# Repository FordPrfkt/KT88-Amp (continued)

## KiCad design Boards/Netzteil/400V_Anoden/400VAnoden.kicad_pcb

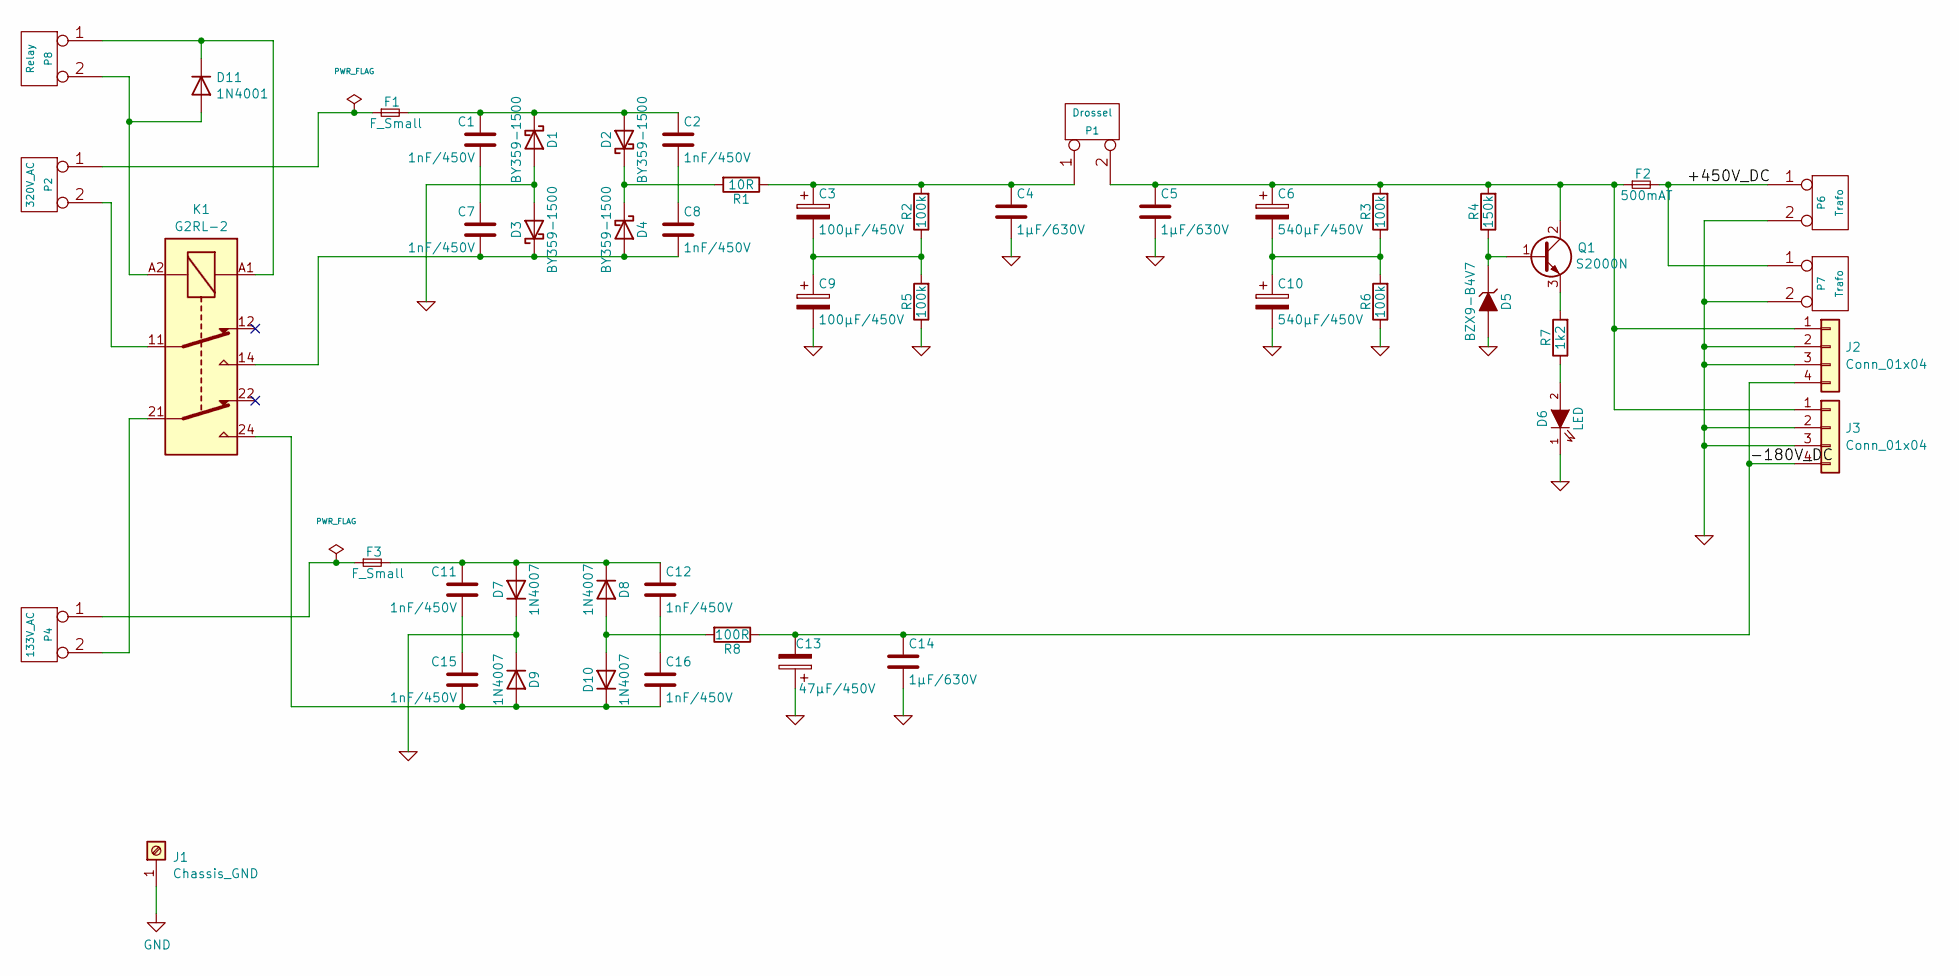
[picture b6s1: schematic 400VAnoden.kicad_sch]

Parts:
C1, C2, C7, C8, C11, C12, C15, C16: 1nF/450V; C_Rect_L10.0mm_W4.0mm_P7.50mm_FKS3_FKP3
C3, C9: 100µF/450V; CP_Radial_D22.0mm_P10.00mm_SnapIn
C4, C5, C14: 1µF/630V; C_Rect_L31.5mm_W11.0mm_P27.50mm_MKS4
C6, C10: 540µF/450V; CP_Radial_D35.0mm_P10.00mm_SnapIn
C13: 47µF/450V; CP_Radial_D16.0mm_P7.50mm
D1, D2, D3, D4: BY359-1500; TO-220-2_Vertical
D5: BZX9-B4V7; D_DO-35_SOD27_P10.16mm_Horizontal
D6: LED; LED_D5.0mm
D7, D8, D9, D10: 1N4007; D_DO-41_SOD81_P10.16mm_Horizontal
D11: 1N4001; D_DO-41_SOD81_P10.16mm_Horizontal
F1, F3: F_Small; Fuse__Holder_Eska_509100
F2: 500mAT; Fuse__Holder_Eska_509100
J1: Chassis_GND; MountingHole_3.2mm_M3_Pad_Via
J2, J3: Conn_01x04; Molex_Mini-Fit_Jr_5566-04A_2x02_P4.20mm_Vertical
K1: G2RL-2; Relay_DPDT_Omron_G2RL-2
P1: Drossel; Molex_Mini-Fit_Jr_5566-02A_2x01_P4.20mm_Vertical
P2: 320V_AC; Molex_Mini-Fit_Jr_5566-02A_2x01_P4.20mm_Vertical
P4: 133V_AC; Molex_Mini-Fit_Jr_5566-02A_2x01_P4.20mm_Vertical
P6, P7: Trafo; Molex_Mini-Fit_Jr_5566-02A_2x01_P4.20mm_Vertical
P8: Relay; Molex_KK-254_AE-6410-02A_1x02_P2.54mm_Vertical
Q1: S2000N; TO-3P-3_Horizontal_TabDown
R1: 10R; R_Axial_DIN0207_L6.3mm_D2.5mm_P10.16mm_Horizontal
R2, R3, R5, R6: 100k; R_Axial_DIN0207_L6.3mm_D2.5mm_P10.16mm_Horizontal
R4: 150k; R_Axial_DIN0207_L6.3mm_D2.5mm_P10.16mm_Horizontal
R7: 1k2; R_Axial_DIN0414_L11.9mm_D4.5mm_P15.24mm_Horizontal
R8: 100R; R_Axial_DIN0207_L6.3mm_D2.5mm_P10.16mm_Horizontal

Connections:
/+450V_DC: F2.2, P6.1, P7.1
/-180V_DC: C13.2, C14.1, J2.4, J3.4, R8.1
GND: C4.2, C5.2, C9.2, C10.2, C13.1, C14.2, D1.2 (A), D3.2 (A), D5.2 (A), D6.1 (K), D7.1 (K), D9.1 (K), J1.1, J2.2, J2.3, J3.2, J3.3, P6.2, P7.2, R5.1, R6.1
unnamed: C1.2, C7.1
unnamed: C2.2, C8.1
unnamed: C3.2, C9.1, R2.1, R5.2
unnamed: C6.2, C10.1, R3.1, R6.2
unnamed: C11.2, C15.1
unnamed: C12.2, C16.1
unnamed: C1.1, C2.1, D1.1 (K), D2.2 (A), F1.2
unnamed: D2.1 (K), D4.1 (K), R1.2
unnamed: C7.2, C8.2, D3.1 (K), D4.2 (A), K1.14
unnamed: D5.1 (K), Q1.1 (B), R4.1
unnamed: D6.2 (A), R7.1
unnamed: C11.1, C12.1, D7.2 (A), D8.1 (K), F3.2
unnamed: D8.2 (A), D10.2 (A), R8.2
unnamed: C15.2, C16.2, D9.2 (A), D10.1 (K), K1.24
unnamed: D11.2 (A), K1.A2, P8.2
unnamed: D11.1 (K), K1.A1, P8.1
unnamed: C5.1, C6.1, F2.1, J2.1, J3.1, P1.2, Q1.2 (C), R3.2, R4.2
unnamed: C3.1, C4.1, P1.1, R1.1, R2.2
unnamed: F1.1, P2.1
unnamed: K1.11, P2.2
unnamed: F3.1, P4.1
unnamed: K1.21, P4.2
unnamed: Q1.3 (E), R7.2

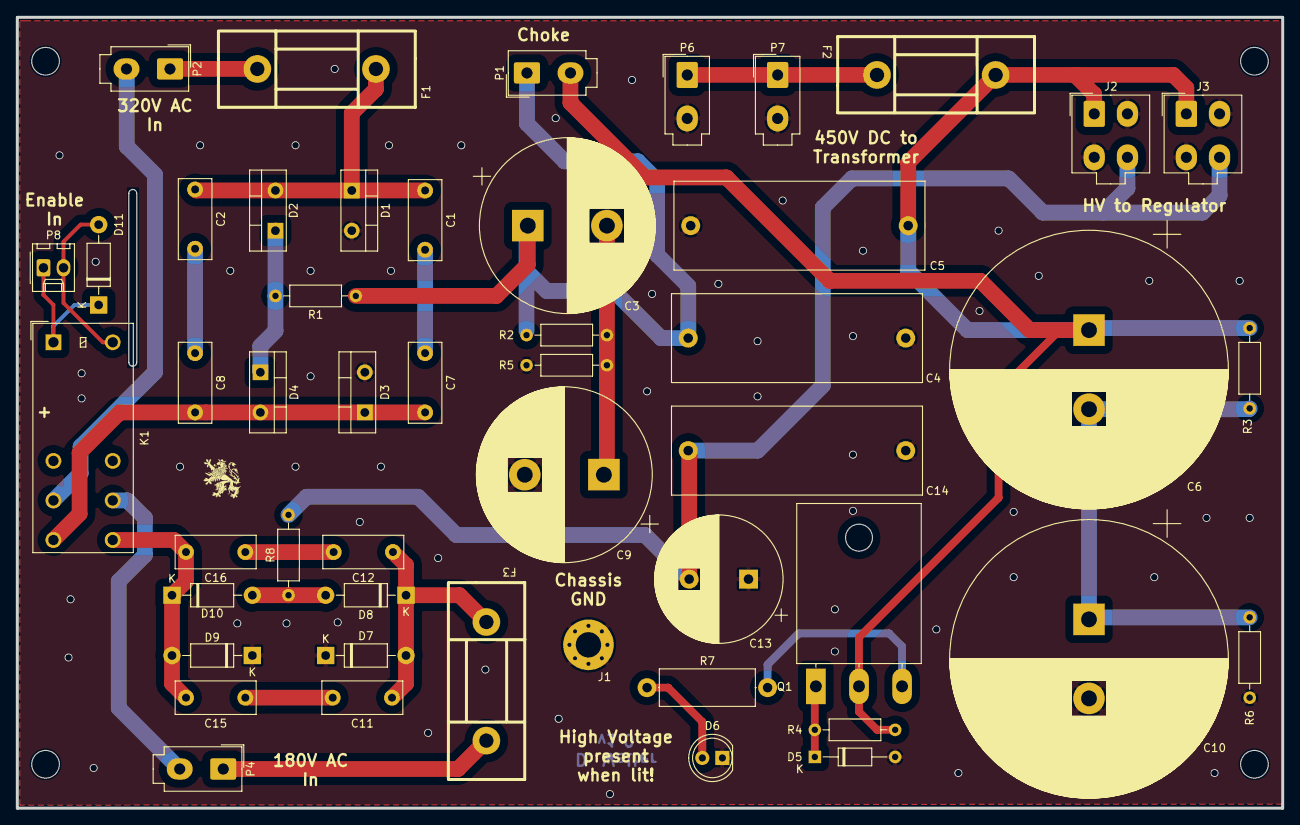
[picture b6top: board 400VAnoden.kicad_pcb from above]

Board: 2 copper layers, 160.0 x 100.0 mm, 49 parts (0 on the bottom side), 26 nets.

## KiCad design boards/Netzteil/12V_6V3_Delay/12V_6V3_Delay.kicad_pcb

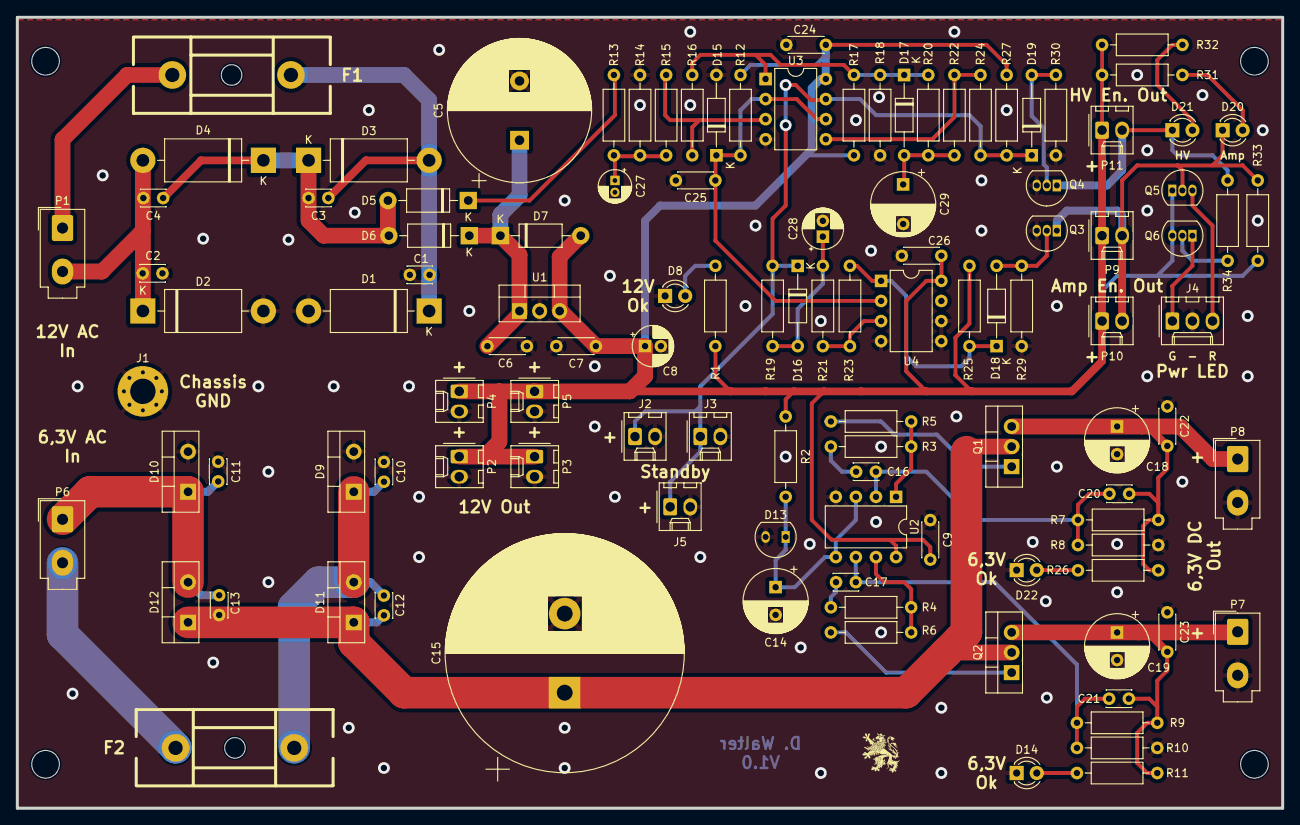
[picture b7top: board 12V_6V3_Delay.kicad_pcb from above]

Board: 2 copper layers, 160.0 x 100.0 mm, 112 parts (0 on the bottom side), 45 nets.

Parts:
C1, C2, C3, C4, C10, C11, C12, C13: 22nF; C_Disc_D3.0mm_W2.0mm_P2.50mm
C5: 4700µF / 63V; CP_Radial_D18.0mm_P7.50mm
C6, C24, C25, C26: 100nF / 63V; C_Disc_D4.3mm_W1.9mm_P5.00mm
C7: Fuse; C_Disc_D4.3mm_W1.9mm_P5.00mm
C8: 47µF / 16V; CP_Radial_D5.0mm_P2.00mm
C9, C22, C23: 100nF; C_Disc_D4.3mm_W1.9mm_P5.00mm
C14: 680µF/16V; CP_Radial_D8.0mm_P3.50mm
C15: 33000µF/16V; CP_Radial_D30.0mm_P10.00mm_SnapIn
C16, C17, C20, C21: 1nF; C_Disc_D3.0mm_W2.0mm_P2.50mm
C18, C19: 680µF; CP_Radial_D8.0mm_P3.50mm
C27: 1µF / 16V; CP_Radial_D4.0mm_P1.50mm
C28: 10µF / 16V; CP_Radial_D5.0mm_P2.00mm
C29: 330µF / 16V; CP_Radial_D8.0mm_P5.00mm
D1, D2, D3, D4: SB350; D_DO-201AD_P15.24mm_Horizontal
D5: SB190; D_DO-41_SOD81_P10.16mm_Horizontal
D6: SB350; D_DO-41_SOD81_P10.16mm_Horizontal
D7: 1N4001; D_DO-41_SOD81_P10.16mm_Horizontal
D8, D14, D20, D21, D22: LED; LED_D3.0mm
D9, D10, D11, D12: MBR1645; TO-220-2_Vertical
D13: LM385Z-1.2; TO-92-2
D15: ZD3V9; D_DO-35_SOD27_P10.16mm_Horizontal
D16, D17: 1N4148; D_DO-35_SOD27_P10.16mm_Horizontal
D18, D19: ZD5V6; D_DO-35_SOD27_P10.16mm_Horizontal
F1, F2: Fuse; Fuse_Holder_Eska_509200
J1: Chassis_GND; MountingHole_3.2mm_M3_Pad_Via
J2, J3, J5: Standby; Molex_KK-254_AE-6410-02A_1x02_P2.54mm_Vertical
J4: Conn_01x03; Molex_KK-254_AE-6410-03A_1x03_P2.54mm_Vertical
P1: 12V5_AC; Molex_Mini-Fit_Jr_5566-02A_2x01_P4.20mm_Vertical
P2: 12V_DC_1; Molex_KK-254_AE-6410-02A_1x02_P2.54mm_Vertical
P3: 12V_DC_2; Molex_KK-254_AE-6410-02A_1x02_P2.54mm_Vertical
P4: 12V_DC_3; Molex_KK-254_AE-6410-02A_1x02_P2.54mm_Vertical
P5: 12V_DC_4; Molex_KK-254_AE-6410-02A_1x02_P2.54mm_Vertical
P6: 7V5_AC; Molex_Mini-Fit_Jr_5566-02A_2x01_P4.20mm_Vertical
P7: 6V3_DC_2; Molex_Mini-Fit_Jr_5566-02A_2x01_P4.20mm_Vertical
P8: 6V3_DC_1; Molex_Mini-Fit_Jr_5566-02A_2x01_P4.20mm_Vertical
P9, P10, P11: Relais; Molex_KK-254_AE-6410-02A_1x02_P2.54mm_Vertical
Q1, Q2: IRF530; TO-220-3_Vertical
Q3, Q4: BS170; TO-92_Inline
Q5: BC337; TO-92_Inline
Q6: BC557; TO-92_Inline
R1, R31: 560R; R_Axial_DIN0207_L6.3mm_D2.5mm_P10.16mm_Horizontal
R2: 22k; R_Axial_DIN0207_L6.3mm_D2.5mm_P10.16mm_Horizontal
R3, R4: 100R; R_Axial_DIN0207_L6.3mm_D2.5mm_P10.16mm_Horizontal
R5, R6, R8, R10: 1k; R_Axial_DIN0207_L6.3mm_D2.5mm_P10.16mm_Horizontal
R7, R9: 4k12; R_Axial_DIN0207_L6.3mm_D2.5mm_P10.16mm_Horizontal
R11, R26: 270R; R_Axial_DIN0207_L6.3mm_D2.5mm_P10.16mm_Horizontal
R12: 4K7; R_Axial_DIN0207_L6.3mm_D2.5mm_P10.16mm_Horizontal
R13: 82K; R_Axial_DIN0207_L6.3mm_D2.5mm_P10.16mm_Horizontal
R14, R29, R30: 100K; R_Axial_DIN0207_L6.3mm_D2.5mm_P10.16mm_Horizontal
R15, R17, R18, R21, R22, R25, R27: 10K; R_Axial_DIN0207_L6.3mm_D2.5mm_P10.16mm_Horizontal
R16: 1M; R_Axial_DIN0207_L6.3mm_D2.5mm_P10.16mm_Horizontal
R19: 330K; R_Axial_DIN0207_L6.3mm_D2.5mm_P10.16mm_Horizontal
R20: 220K; R_Axial_DIN0207_L6.3mm_D2.5mm_P10.16mm_Horizontal
R23, R24: 5M1; R_Axial_DIN0207_L6.3mm_D2.5mm_P10.16mm_Horizontal
R32: 560; R_Axial_DIN0207_L6.3mm_D2.5mm_P10.16mm_Horizontal
R33, R34: 4k7; R_Axial_DIN0207_L6.3mm_D2.5mm_P10.16mm_Horizontal
U1: LM7812CT; TO-220-3_Vertical
U2: LMC6482; DIP-8_W7.62mm
U3, U4: LM393; DIP-8_W7.62mm

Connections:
12V_Rect: D5.1 (K), R13.1
+12V: C7.1, C8.1, C9.2, C24.1, C26.1, D7.2 (A), P2.1, P3.1, P4.1, P5.1, P9.1, P10.1, P11.1, Q5.1 (C), Q6.3 (E), R1.1, R2.2, R12.1, R17.2, R25.1, R27.1, R31.1, R32.1, R33.2, U1.3 (OUT), U2.8 (V+), U3.8 (V+), U4.8 (V+)
/6V3/Reference: C14.1, D13.1 (K), R2.1, U2.3 (+), U2.5 (+)
/6V3/V_Unreg: C12.2, C13.1, C15.1, D11.1 (K), D12.1 (K), Q1.2 (D), Q2.2 (D)
/Delay/LED_G: J4.1, Q6.1 (C)
/Delay/LED_R: J4.3, Q5.3 (E)
/Delay/Vref: C25.1, D15.1 (K), R12.2, U3.2 (-), U3.6 (_), U4.2 (-)
GND: C1.2, C2.1, C5.2, C6.2, C7.2, C8.2, C9.1, C10.2, C11.1, C14.2, C15.2, C18.2, C19.2, C22.1, C23.1, C24.2, C25.2, C26.2, C27.2, C28.2, C29.2, D1.2 (A), D2.2 (A), D8.1 (K), D9.2 (A), D10.2 (A), D13.2 (A), D14.1 (K), D15.2 (A), D22.1 (K), J1.1, J2.2, J3.2, J4.2, J5.2, P2.2, P3.2, P4.2, P5.2, P7.2, P8.2, Q3.3 (S), Q4.3 (S), R8.1, R10.1, R14.2, R18.1, R29.2, R30.2, U1.2 (GND), U2.4 (V-), U3.4 (V-), U4.4 (V-), U4.5 (+), U4.6 (_)
unnamed: C16.1, R3.1
unnamed: C17.1, R4.1
unnamed: C27.1, R13.2, R14.1, R15.2
unnamed: C1.1, C3.1, D1.1 (K), D3.2 (A), F1.2
unnamed: C2.2, C4.2, D2.1 (K), D4.2 (A), P1.2
unnamed: C3.2, C4.1, D3.1 (K), D4.1 (K), D5.2 (A), D6.2 (A)
unnamed: C5.1, C6.1, D6.1 (K), D7.1 (K), U1.1 (IN)
unnamed: D8.2 (A), R1.2
unnamed: C11.2, C13.2, D10.1 (K), D12.2 (A), P6.1
unnamed: C10.1, C12.1, D9.1 (K), D11.2 (A), F2.1
unnamed: D14.2 (A), R11.2
unnamed: C28.1, D16.2 (A), R19.2, R21.1
unnamed: D16.1 (K), D19.1 (K), J2.1, J3.1, J5.1, R19.1, R24.2, R27.2, U3.7
unnamed: C29.1, D17.2 (A), R20.2, R22.1
unnamed: D17.1 (K), R16.1, R17.1, R18.2, R20.1, U3.1
unnamed: D18.2 (A), Q3.2 (G), R29.1
unnamed: D18.1 (K), R23.2, R25.2, U4.1
unnamed: D19.2 (A), Q4.2 (G), R30.1
unnamed: D20.2 (A), R31.2
unnamed: D20.1 (K), P9.2, P10.2, Q3.1 (D), Q5.2 (B), R33.1
unnamed: D21.2 (A), R32.2
unnamed: D21.1 (K), P11.2, Q4.1 (D), R34.2
unnamed: D22.2 (A), R26.2
unnamed: F1.1, P1.1
unnamed: F2.2, P6.2
unnamed: C19.1, C21.2, C23.2, P7.1, Q2.3 (S), R9.2, R11.1
unnamed: C18.1, C20.2, C22.2, P8.1, Q1.3 (S), R7.2, R26.1
unnamed: Q1.1 (G), R5.1
unnamed: Q2.1 (G), R6.1
unnamed: Q6.2 (B), R34.1
unnamed: R3.2, R5.2, U2.1
unnamed: R4.2, R6.2, U2.7
unnamed: C16.2, C20.1, R7.1, R8.2, U2.2 (-)
unnamed: C17.2, C21.1, R9.1, R10.2, U2.6 (-)
unnamed: R15.1, R16.2, U3.3 (+)
unnamed: R22.2, R24.1, U3.5 (+)
unnamed: R21.2, R23.1, U4.3 (+)

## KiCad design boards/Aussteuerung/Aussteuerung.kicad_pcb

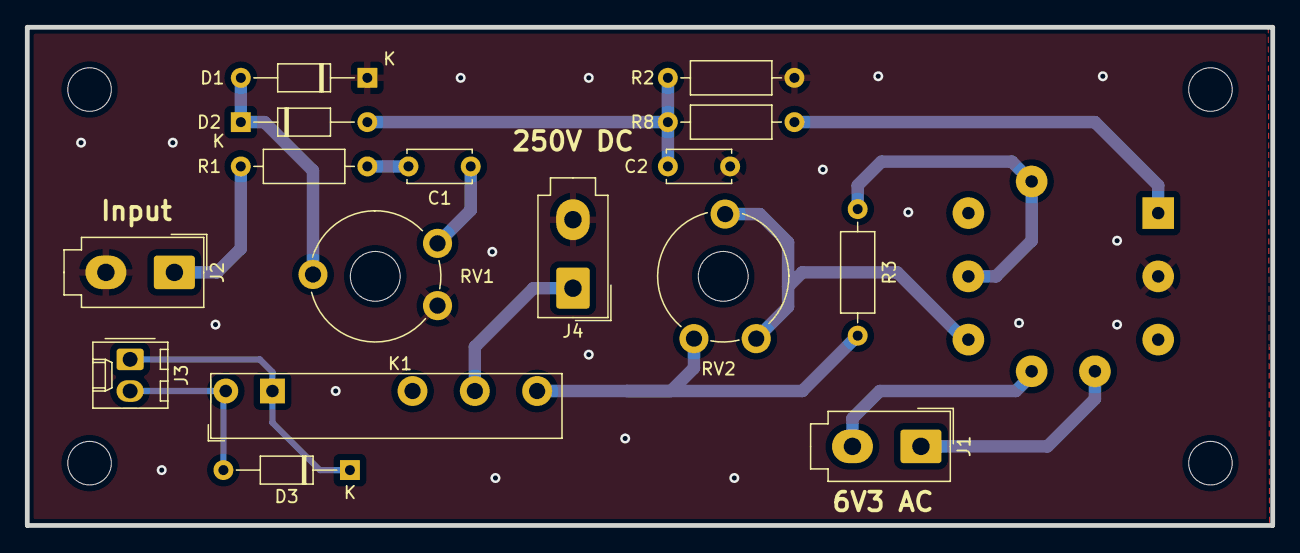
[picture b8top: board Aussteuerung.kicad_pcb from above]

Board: 2 copper layers, 100.0 x 40.0 mm, 17 parts (1 on the bottom side), 15 nets.

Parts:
C1: 100nF / 500V; C_Disc_D5.0mm_W2.5mm_P5.00mm
C2: 220nF; C_Disc_D5.0mm_W2.5mm_P5.00mm
D1, D2: 1N4007; D_DO-35_SOD27_P10.16mm_Horizontal
D3: D; D_DO-35_SOD27_P10.16mm_Horizontal
J1: 6V3_Heater; Molex_Mini-Fit_Jr_5566-02A_2x01_P4.20mm_Vertical
J2: Signal_R; Molex_Mini-Fit_Jr_5566-02A_2x01_P4.20mm_Vertical
J3: Signal_R; Molex_KK-254_AE-6410-02A_1x02_P2.54mm_Vertical
J4: 250VDC; Molex_Mini-Fit_Jr_5566-02A_2x01_P4.20mm_Vertical
K1: FINDER-34.51; Relay_SPDT_Finder_34.51_Vertical
R1: 100k; R_Axial_DIN0207_L6.3mm_D2.5mm_P10.16mm_Horizontal
R2, R8: 1M; R_Axial_DIN0207_L6.3mm_D2.5mm_P10.16mm_Horizontal
R3: 470k; R_Axial_DIN0207_L6.3mm_D2.5mm_P10.16mm_Horizontal
RV1: 220k; Potentiometer_Piher_PT-10-V10_Vertical_Hole
RV2: 47k; Potentiometer_Piher_PT-10-V10_Vertical_Hole
U1: EM84; Valve_Noval_P

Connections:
GND: C2.2, D1.1, J2.2, J4.2, R2.2, RV1.3, U1.2
unnamed: C1.1, R1.2
unnamed: C1.2, RV1.1
unnamed: C2.1, D2.2, R2.1, R8.1
unnamed: D1.2, D2.1, RV1.2
unnamed: D3.1, J3.1, K1.A1
unnamed: D3.2, J3.2, K1.A2
unnamed: J1.1, U1.4
unnamed: J1.2, U1.5
unnamed: J2.1, R1.1
unnamed: J4.1, K1.11
unnamed: K1.14, R3.1, RV2.3
unnamed: R3.2, U1.7, U1.9
unnamed: R8.2, U1.1
unnamed: RV2.1, RV2.2, U1.6

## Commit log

2016-02-11 Anoden-Stabi auf eigenes Board, Endstufe Layouttest
2016-02-27 Layouting...
2016-05-03 Updated Layout
2016-08-27 Work in Progress
2016-10-06 Bias-Anzeige erstellt
2016-10-08 New Layout of Bias Board
2016-10-08 New Potis
2019-04-22 Converted to Kicad 5.1 and Layout changes
2019-04-24 Layout changes after migrate to Kicad 5.1
2019-09-23 Minor Layout changes
2019-10-21 Layout changes, Supply connector changes, Mounting holes
2019-11-13 HV Switch on delay added
2019-11-23 Added Vias & Mounting Holes
2019-11-29 Added Test, moved mounting holes
2019-12-05 New Volume Control Board
2019-12-15 Added Power LEDs
2020-01-27 Adjusted Silkscreen
2021-02-27 Added Mounting holes, Moved -60V Divider to HV Board, eliminated +450V Connector and Feedback Connector on Amp Board
2021-04-20 6,3V und 12V auf einer Platine zusammengefasst
2021-05-21 Reworked Delay + Layout changed
2021-11-07 Work in progess - many LAyour changes
2024-11-20 6.3V, 400V und 400V Regler Boards bestellt
2025-02-26 Leiterplatten erstellt
2025-02-26 Leiterplatte erstellt
